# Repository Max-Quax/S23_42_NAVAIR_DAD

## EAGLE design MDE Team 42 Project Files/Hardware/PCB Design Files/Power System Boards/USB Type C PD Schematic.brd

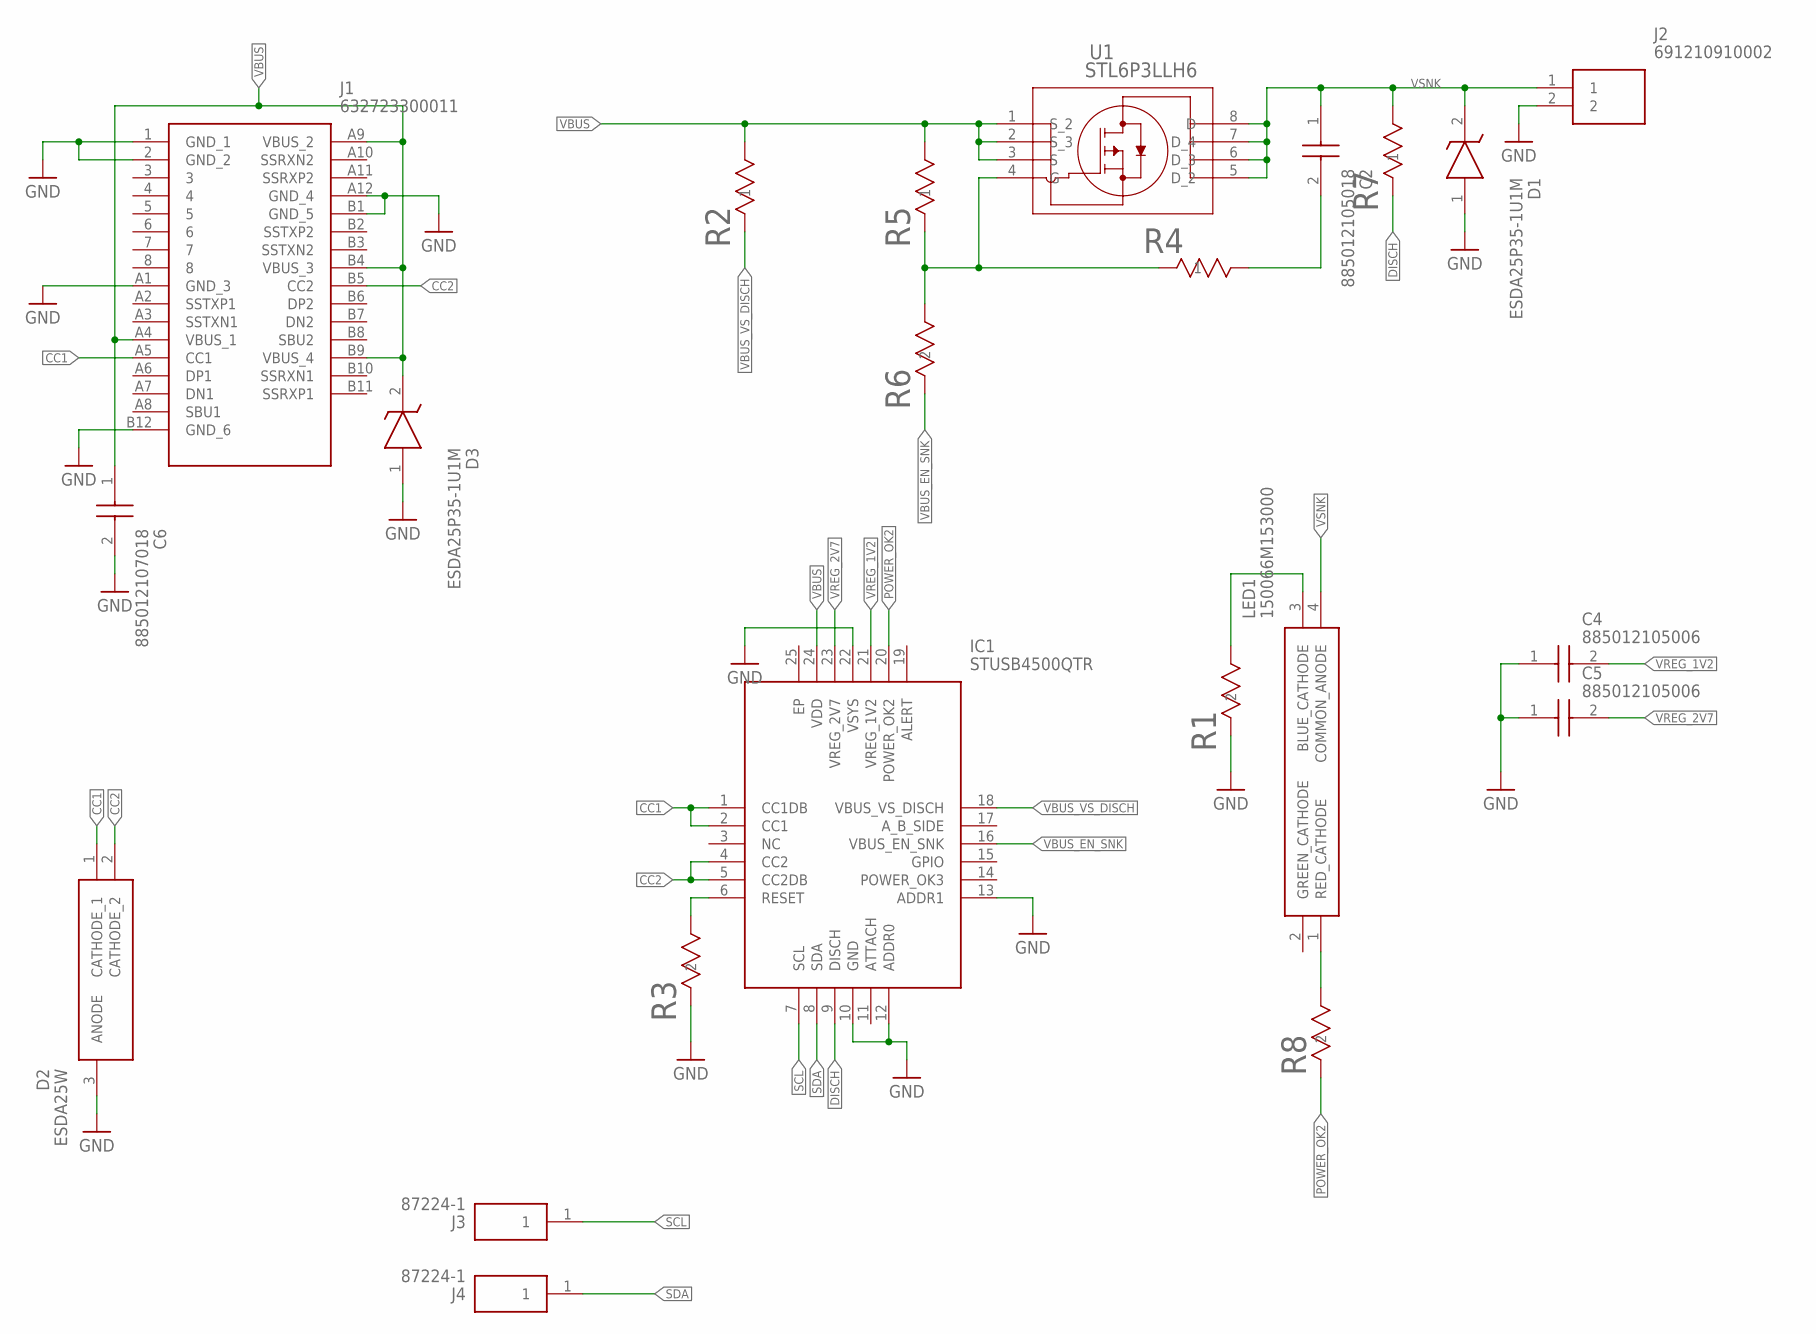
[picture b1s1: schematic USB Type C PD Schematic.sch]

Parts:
C2: 885012105018; CAPC1005X55N
C4, C5: 885012105006; CAPC1005X55N
C6: 885012107018; CAPC2012X145N
D1, D3: ESDA25P35-1U1M; ESDA8P801U1M
D2: ESDA25W; SOT65P210X110-3N
IC1: STUSB4500QTR; QFN50P400X400X100-25N
J1: 632723300011
J2: 691210910002
J3, J4: 87224-1; HDRV1W66P0X254_1X1_213X254X107
LED1: 150066M153000
R1, R6, R8: RC0402JR-0722KL; RC0402N_YAG
R2, R7: RNCP0603FTD1K00; STA_RNCP0603_STP
R3: RC0402JR-0710KL; RC0402N_YAG
R4: RC0201FR-07100RL; YAG_R0201_YAG
R5: RC0603FR-07100KL; RC0603N_YAG
U1: STL6P3LLH6; POWERFLAT_3P3X3P3_STM

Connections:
CC1: D2.1 (CATHODE_1), IC1.1 (CC1DB), IC1.2 (CC1), J1.A5 (CC1)
CC2: D2.2 (CATHODE_2), IC1.4 (CC2), IC1.5 (CC2DB), J1.B5 (CC2)
DISCH: IC1.9 (DISCH), R7.1
GND: C4.1, C5.1, C6.2, D1.1 (A), D2.3 (ANODE), D3.1 (A), IC1.10 (GND), IC1.12 (ADDR0), IC1.13 (ADDR1), IC1.22 (VSYS), J1.1 (GND_1), J1.2 (GND_2), J1.A1 (GND_3), J1.A12 (GND_4), J1.B1 (GND_5), J1.B12 (GND_6), J2.2, R1.2, R3.2
unnamed: LED1.3 (BLUE_CATHODE), R1.1
unnamed: IC1.6 (RESET), R3.1
unnamed: LED1.1 (RED_CATHODE), R8.1
unnamed: R4.1, R5.1, R6.1, U1.4 (G)
unnamed: C2.2, R4.2
POWER_OK2: IC1.20 (POWER_OK2), R8.2
SCL: IC1.7 (SCL), J3.1
SDA: IC1.8 (SDA), J4.1
VBUS: C6.1, D3.2 (K), IC1.24 (VDD), J1.A4 (VBUS_1), J1.A9 (VBUS_2), J1.B4 (VBUS_3), J1.B9 (VBUS_4), R2.2, R5.2, U1.1 (S_2), U1.2 (S_3), U1.3 (S)
VBUS_EN_SNK: IC1.16 (VBUS_EN_SNK), R6.2
VBUS_VS_DISCH: IC1.18 (VBUS_VS_DISCH), R2.1
VREG_1V2: C4.2, IC1.21 (VREG_1V2)
VREG_2V7: C5.2, IC1.23 (VREG_2V7)
VSNK: C2.1, D1.2 (K), J2.1, LED1.4 (COMMON_ANODE), R7.2, U1.5 (D_2), U1.6 (D_3), U1.7 (D_4), U1.8 (D)

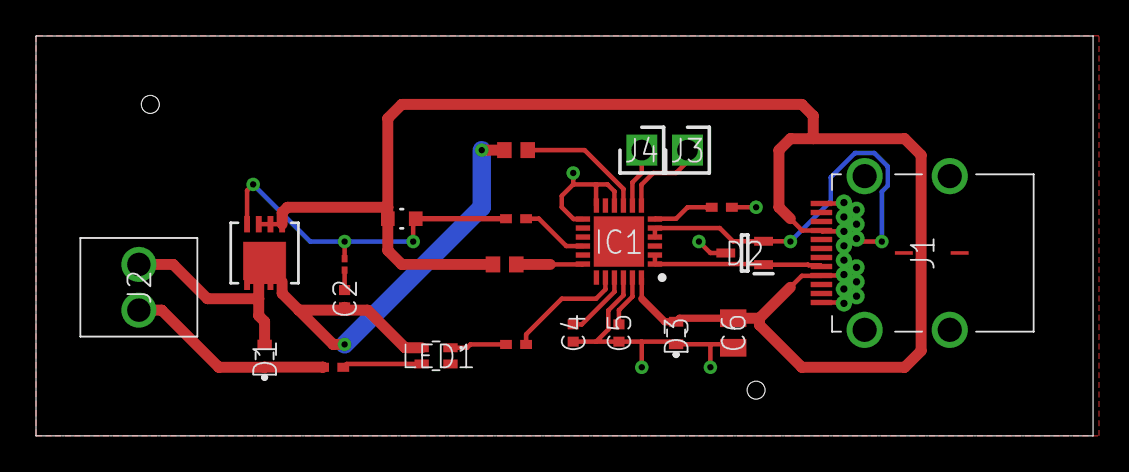
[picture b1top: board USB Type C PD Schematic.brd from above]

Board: 2 copper layers, 58.7 x 22.2 mm, 22 parts (0 on the bottom side), 18 nets.

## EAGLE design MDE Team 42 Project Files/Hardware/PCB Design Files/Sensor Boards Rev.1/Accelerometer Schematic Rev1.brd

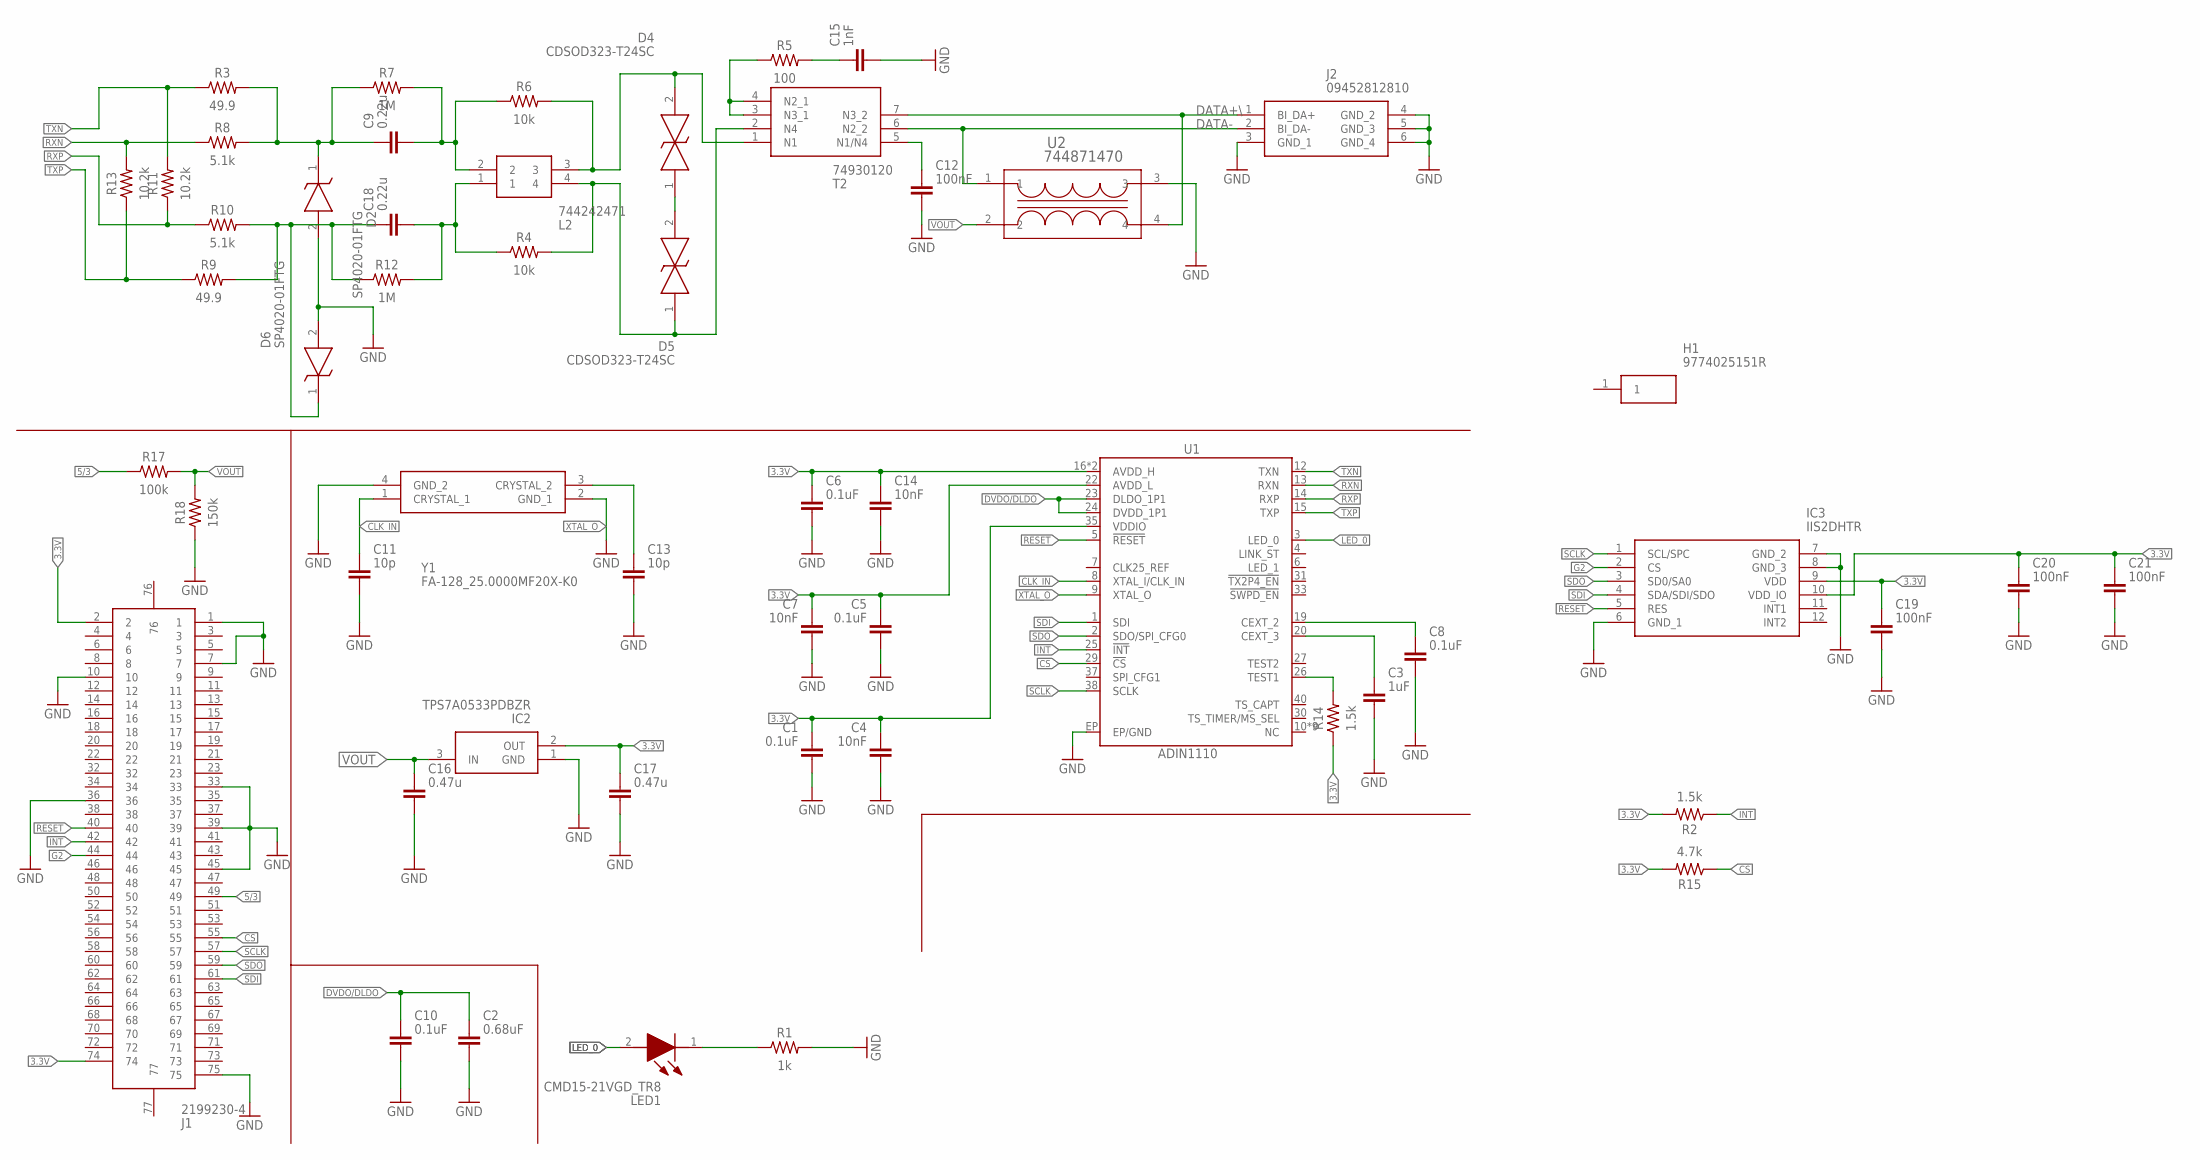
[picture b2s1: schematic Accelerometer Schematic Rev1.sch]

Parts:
C1, C5, C6, C8, C10: 0.1uF; CAPC1005X60
C2: 0.68uF; CAPC1005X60
C3: 1uF; CAPC1005X60
C4, C7, C14: 10nF; CAPC1005X60
C9, C18: 0.22u; CAPC1005X60
C11, C13: 10p; CAPC1005X60
C12, C19, C20, C21: 100nF; CAPC1005X60
C15: 1nF; CAPC1005X60
C16, C17: 0.47u; CAPC1005X60
D2, D6: SP4020-01FTG; SOD2613X114N
D4, D5: CDSOD323-T24SC; SOD2513X114N
H1: 9774025151R
IC2: TPS7A0533PDBZR; SOT95P237X112-3N
IC3: IIS2DHTR; LGA-12
J1: 2199230-4; 21992304
J2: 09452812810
L2: 744242471
LED1: CMD15-21VGD_TR8; LEDC3215X130N
R1: 1k; RESC1005X40
R2, R14: 1.5k; RESC1005X40
R3, R9: 49.9; RESC1005X40
R4, R6: 10k; RESC1005X40
R5: 100; RESC1005X40
R7, R12: 1M; RESC1005X40
R8, R10: 5.1k; RESC1005X40
R11, R13: 10.2k; RESC1005X40
R15: 4.7k; RESC1005X40
R17: 100k; RESC1005X40
R18: 150k; RESC1005X40
T2: 74930120
U1: ADIN1110; LFCSP-40
U2: 744871470; SMT_871470_WRE
Y1: FA-128_25.0000MF20X-K0; FA128250000MF20XK0

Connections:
3.3V: C1.1, C4.1, C5.1, C6.1, C7.1, C14.1, C17.1, C19.1, C20.1, C21.1, IC2.2 (OUT), IC3.9 (VDD), IC3.10 (VDD_IO), J1.2, J1.74, R2.2, R14.1, R15.2, U1.16 (AVDD_H), U1.17 (AVDD_H), U1.22 (AVDD_L), U1.35 (VDDIO)
5/3: J1.49, R17.1
CLK_IN: C11.1, U1.8 (XTAL_I/CLK_IN), Y1.1 (CRYSTAL_1)
CS: J1.55, R15.1, U1.29 (!CS!)
DATA+\: J2.1 (BI_DA+), T2.7 (N3_2), U2.4
DATA-: J2.2 (BI_DA-), T2.6 (N2_2), U2.1
DVDO/DLDO: C2.1, C10.1, U1.23 (DLDO_1P1), U1.24 (DVDD_1P1)
G2: IC3.2 (CS), J1.44
GND: C1.2, C2.2, C3.2, C4.2, C5.2, C6.2, C7.2, C8.2, C10.2, C11.2, C12.2, C13.2, C14.2, C15.2, C16.2, C17.2, C19.2, C20.2, C21.2, D2.2 (A), D6.2 (A), IC2.1 (GND), IC3.6 (GND_1), IC3.7 (GND_2), IC3.8 (GND_3), J1.1, J1.7, J1.10, J1.33, J1.36, J1.39, J1.45, J1.75, J2.3 (GND_1), J2.4 (GND_2), J2.5 (GND_3), J2.6 (GND_4), R1.2, R18.1, U1.EP (EP/GND), U2.3, Y1.2 (GND_1), Y1.4 (GND_2)
INT: J1.42, R2.1, U1.25 (!INT!)
LED_0: LED1.2 (A), U1.3 (LED_0)
unnamed: C15.1, R5.2
unnamed: LED1.1 (K), R1.1
unnamed: C18.2, L2.1, R4.1, R12.2
unnamed: R14.2, U1.26 (TEST1)
unnamed: C9.2, L2.2, R6.1, R7.2
unnamed: D5.1, L2.4, R4.2, T2.2 (N4)
unnamed: C8.1, U1.19 (CEXT_2)
unnamed: C3.1, U1.20 (CEXT_3)
unnamed: C9.1, D2.1 (K), R3.2, R7.1, R8.2
unnamed: C12.1, T2.5 (N1/N4)
unnamed: R5.1, T2.3 (N3_1), T2.4 (N2_1)
unnamed: C18.1, D6.1 (K), R9.2, R10.2, R12.1
unnamed: D4.2, L2.3, R6.2, T2.1 (N1)
unnamed: D4.1, D5.2
RESET: IC3.5 (RES), J1.40, U1.5 (!RESET!)
RXN: R8.1, R13.2, U1.13 (RXN)
RXP: R10.1, R11.1, U1.14 (RXP)
SCLK: IC3.1 (SCL/SPC), J1.57, U1.38 (SCLK)
SDI: IC3.4 (SDA/SDI/SDO), J1.61, U1.1 (SDI)
SDO: IC3.3 (SD0/SA0), J1.59, U1.2 (SDO/SPI_CFG0)
TXN: R3.1, R11.2, U1.12 (TXN)
TXP: R9.1, R13.1, U1.15 (TXP)
VOUT: C16.1, IC2.3 (IN), R17.2, R18.2, U2.2
XTAL_O: C13.1, U1.9 (XTAL_O), Y1.3 (CRYSTAL_2)

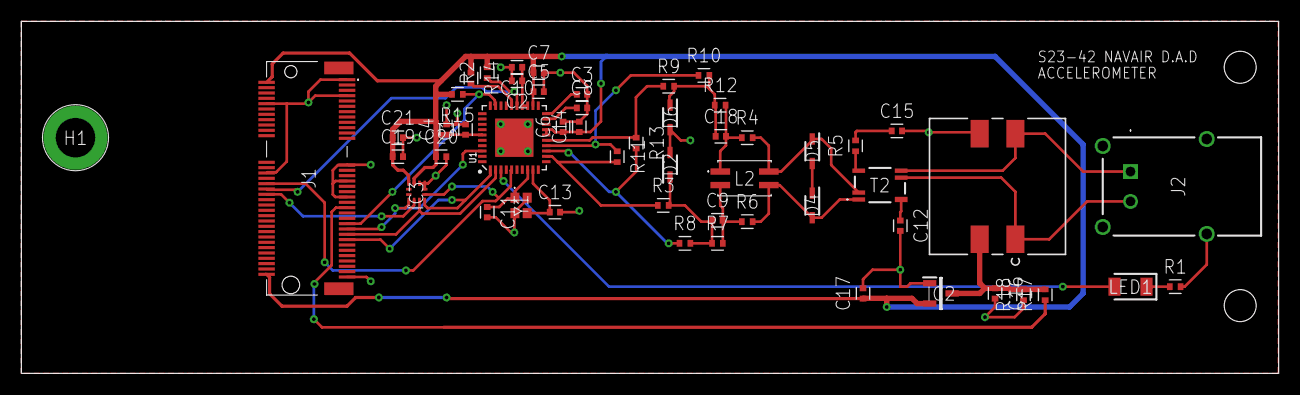
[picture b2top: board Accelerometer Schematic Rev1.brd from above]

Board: 2 copper layers, 117.9 x 33.0 mm, 53 parts (0 on the bottom side), 35 nets.

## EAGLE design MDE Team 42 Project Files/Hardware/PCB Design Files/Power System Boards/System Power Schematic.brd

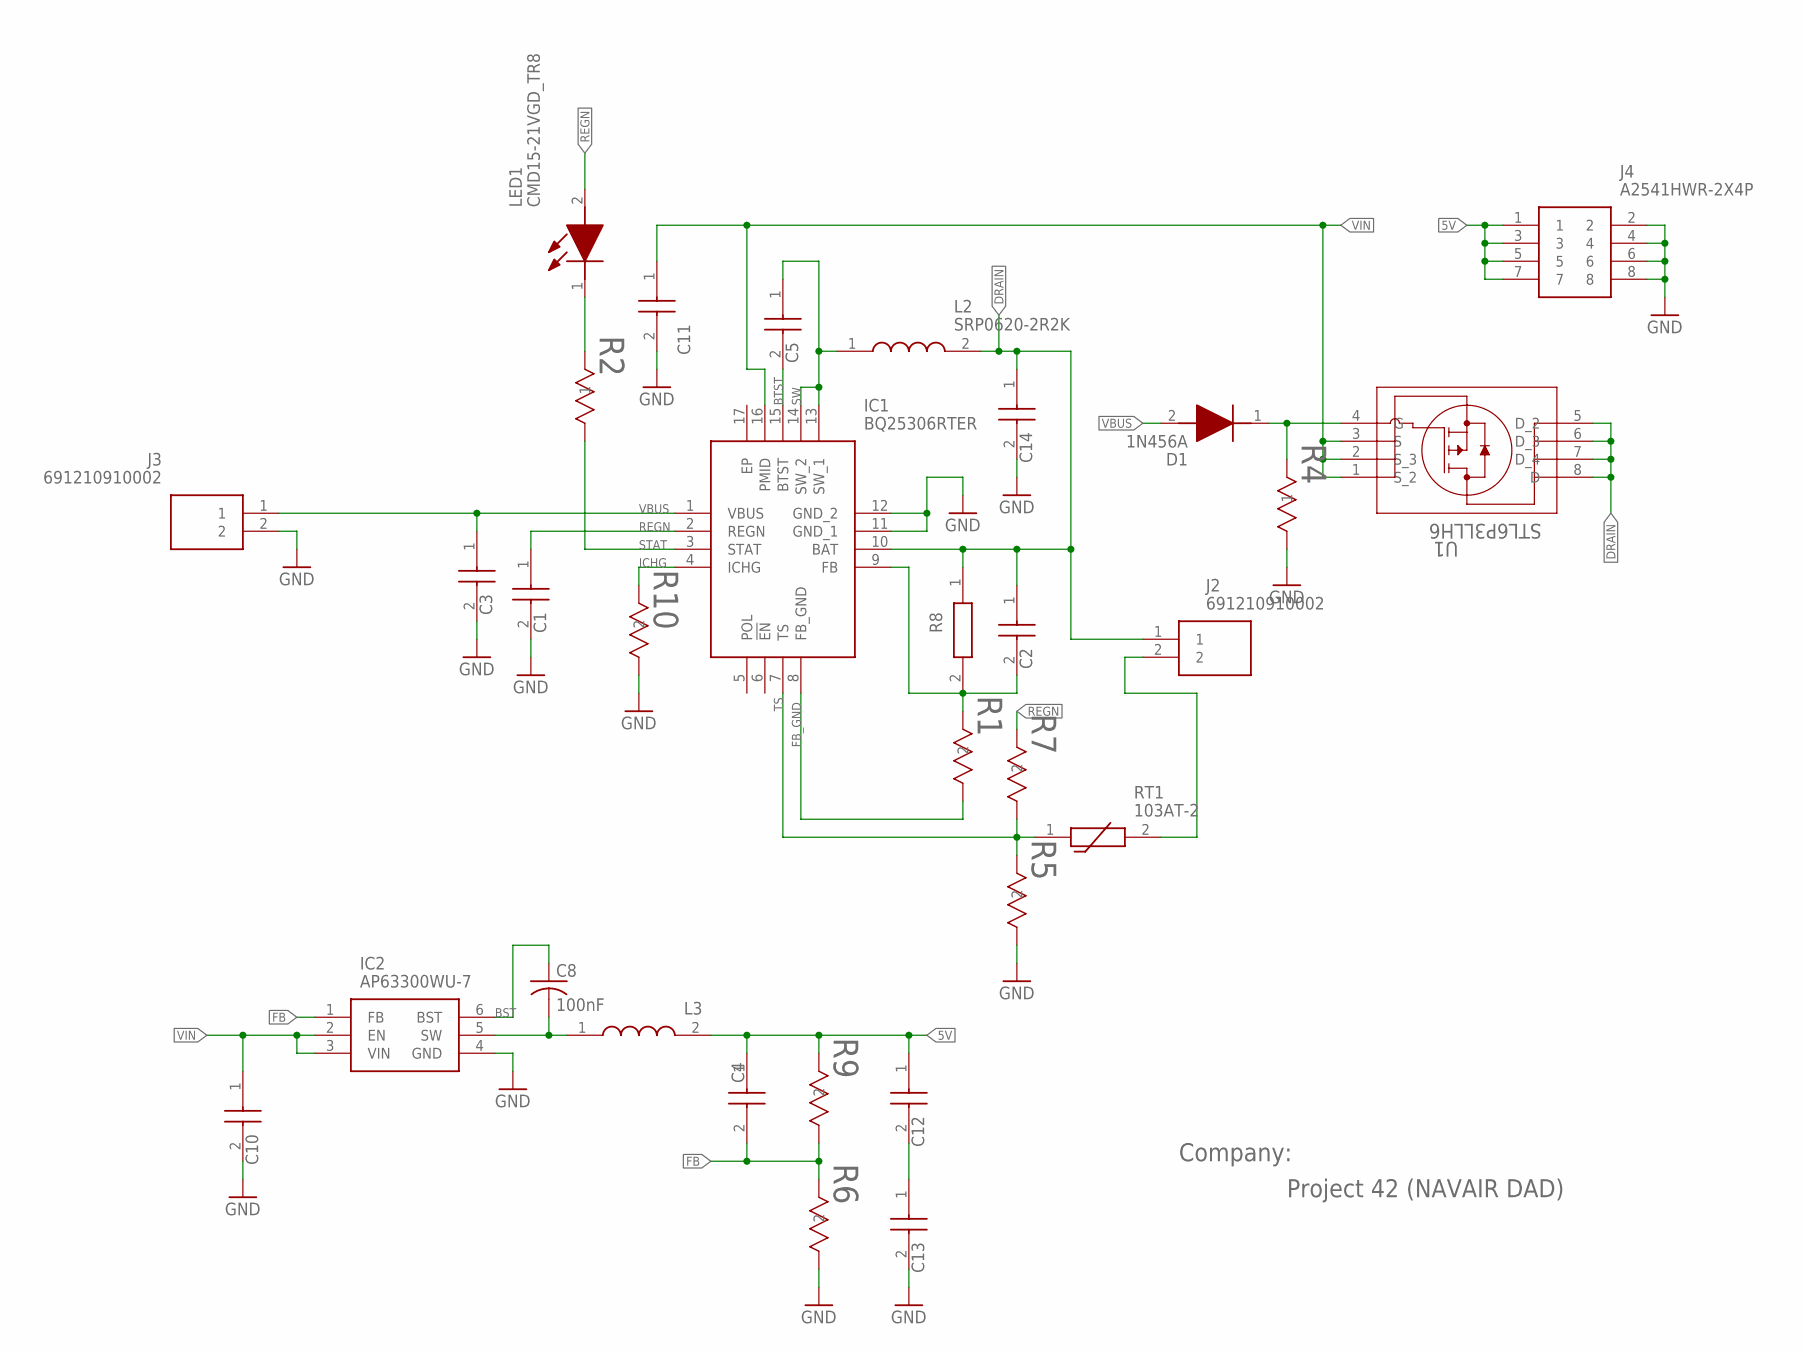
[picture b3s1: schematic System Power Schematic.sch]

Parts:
C1, C3: TMK107ABJ225KA-T; CAPC1608X90N
C2: CGA1A2X7R1H471K030BA; CAPC1608X90N
C4: CL05C470JB5NNNC; CAPC1005X55N
C5: 885012107018; CAPC2012X145N
C8: 100nF; C0805
C10, C11, C14: CL21A106KAYNNNG; CAPC2012X145N
C12, C13: CL31A226KAHNNNE; CAPC3216X180N
D1: 1N456A; DIO_1N456A
IC1: BQ25306RTER; QFN50P300X300X80-17N
IC2: AP63300WU-7; SOT95P280X90-6N
J2, J3: 691210910002
J4: A2541HWR-2X4P; RHDRRA8W64P254_2X4_1066X850X52
L2: SRP0620-2R2K; SRP06202R2K
L3: SRP0615-6R8K; SRP06152R2K
LED1: CMD15-21VGD_TR8; LEDC3215X130N
R1: ERA-3AEB204V; RC0603N_PAN
R2: RNCP0603FTD1K00; STA_RNCP0603_STP
R4: PNM0603E5001BST5; 0603_VIS
R5: RC0603FR-0712K4L; RC0603N_YAG
R6: RC0603FR-0730K1L; RC0603N_YAG
R7: RC0603FR-073K48L; RC0603N_YAG
R8: RK73H1JTTD1334F; RESC1608X55N
R9: RC0603FR-07158KL; RC0603N_YAG
R10: RN73C1J13K3BTDF; RES0603_RN73_TYCO_TYC
RT1: 103AT-2; 103AT2
U1: STL6P3LLH6; POWERFLAT_3P3X3P3_STM

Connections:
5V: C4.1, C12.1, J4.1, J4.3, J4.5, J4.7, L3.2, R9.2
BST: C8.1, IC2.6 (BST)
BTST: C5.2, IC1.15 (BTST)
DRAIN: C2.1, C14.1, IC1.10 (BAT), J2.1, L2.2, R8.1, U1.5 (D_2), U1.6 (D_3), U1.7 (D_4), U1.8 (D)
FB: C4.2, IC2.1 (FB), R6.2, R9.1
FB_GND: IC1.8 (FB_GND), R1.1
GND: C1.2, C3.2, C10.2, C11.2, C13.2, C14.2, IC1.11 (GND_1), IC1.12 (GND_2), IC2.4 (GND), J3.2, J4.2, J4.4, J4.6, J4.8, R4.2, R5.1, R6.1, R10.1
ICHG: IC1.4 (ICHG), R10.2
unnamed: LED1.1 (K), R2.1
unnamed: C12.2, C13.1
unnamed: D1.1 (K), R4.1, U1.4 (G)
unnamed: J2.2, RT1.2
unnamed: C2.2, IC1.9 (FB), R1.2, R8.2
unnamed: C8.2, IC2.5 (SW), L3.1
REGN: C1.1, IC1.2 (REGN), LED1.2 (A), R7.2
STAT: IC1.3 (STAT), R2.2
SW: C5.1, IC1.13 (SW_1), IC1.14 (SW_2), L2.1
TS: IC1.7 (TS), R5.2, R7.1, RT1.1
VBUS: C3.1, D1.2 (A), IC1.1 (VBUS), J3.1
VIN: C10.1, C11.1, IC1.16 (PMID), IC2.2 (EN), IC2.3 (VIN), U1.1 (S_2), U1.2 (S_3), U1.3 (S)

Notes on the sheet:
Company:
Project 42 (NAVAIR DAD)

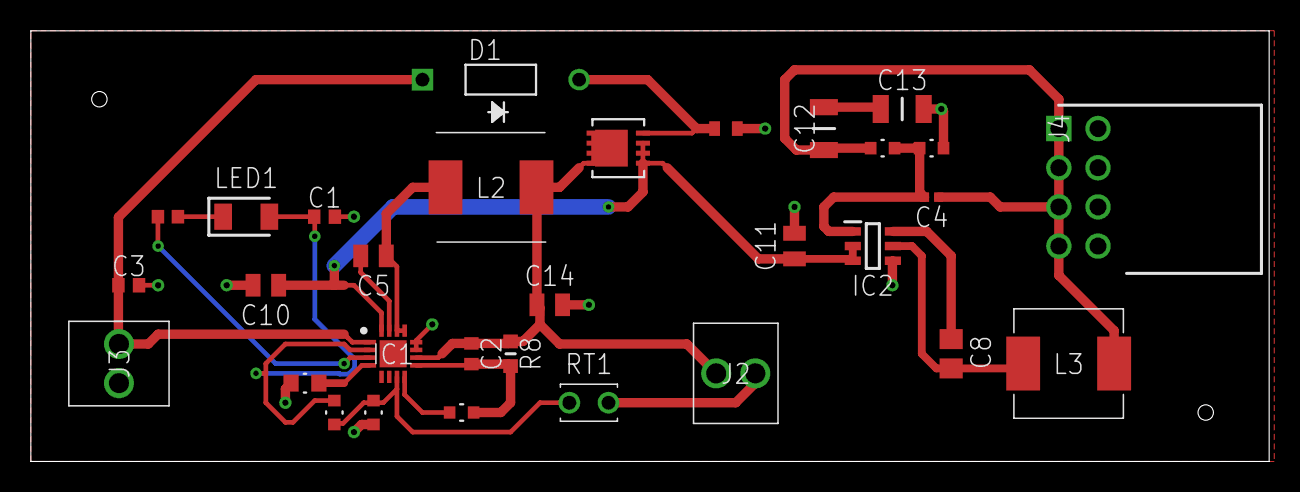
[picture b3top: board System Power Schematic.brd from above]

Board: 2 copper layers, 80.3 x 27.9 mm, 31 parts (0 on the bottom side), 20 nets.

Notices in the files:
parts and their libraries:
COPYRIGHT: Copyright (C) 2023 Ultra Librarian. All rights reserved.
